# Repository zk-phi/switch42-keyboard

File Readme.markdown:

Switch42 Keyboard の紹介＆組み立てガイド

(これは基板バージョン rev3 ベースの紹介です)

# 概要

Switch42 は zk-phi が初めて設計した自作キーボードキットです。

以下の特徴があります：

- 直行配列・分割キーボード

- Corne Keyboard などとちょうど同じ 42 キー
  - (ホームポジションからひとマスで到達できる行・列が過不足なくついています)

- 指の腹で押せるよう、少し張り出して配置した親指キー

- フルカラー LED / LED テープに対応

- ProMicro を下部に格納し、スッキリした外観

- MX 互換スイッチ専用

- (非リバーシブル基板で表裏を間違いづらい)

LED 以外には表面実装品を使わないので、組み立て難易度は初〜中級者向けだと思います。二箇所だけ一般的な自作キーボードキットには出てこない作業が登場します：

- 基板の不要部分をカットする作業
- Pro Micro と干渉する部品の足をカット・絶縁

# 設計の経緯＆工夫など
## なぜ作ったの？

Ergo42 で自作キーボードデビューしてから、よりキー数の少ない Corne に挑戦し、使っているうちにこんな実感が湧いてきました：

- このキー数でも十分仕事になるけど、これより少ないくなると自分には辛いな
  - = これがコンパクトさと実用性の落としどころだな

6 x 3 + 3 というキー配列に大満足していた一方で、だんだんと Ergo42 の格子配列も恋しくなってきたりもして、ヨシそれなら「格子配列の 42 キー」を作ってみよう、と設計に挑戦しました。

オリジナルな工夫もなにか入れたいなということで、以前から気になっていた「親指キー押しづらい問題」に対する自分なりのアイデア（張り出させて配置する）も盛り込んでみました。

また、それまで LED のハンダづけにビビってキーボードを光らせてこなかったのですが、自分で設計すればきっと試作基板がたくさん余るので失敗も怖くないぞ！ということで、初のキーボード設計から LED 対応に挑戦しました。

同じ「格子配列＋親指キー」ということで、 コンセプトの近い MiniAxe を組むことも考えたのですが、以下のポイントが決め手になって、自分で設計することにしました：

- ６列キーボードが絶対必要だったこと

自分は Emacs のヘビーユーザーで、 Alt-Ctrl-, Alt-Shift- などの複雑な組み合わせにもいちいちショートカットを設定しているので、 Ctrl, Shift を小指で押せる仕様がマストでした。

- Pro Micro を採用したかったこと

MiniAxe は定番のマイコンボード "Pro Micro" を採用しない、より進んだ設計になっています。これによって、とても薄く、「モゲ」問題とも無縁なキーボードを実現しています。一方、半田付け難易度は Pro Micro を使用したキーボードよりも上がっていて、組み立てられるか不安だったのと、自分以上に初心者な友人に提供したかったこともあったので、オーソドックスな Pro Micro (コンスルー) を採用したいモチベーションがありました。

## 設計上の工夫

リバーシブル基板をやめて、代わりに基板の不要部分を切り取れるようにしました。もともとは ProMicro を下部に格納しつつコンスルーに対応するために考えた仕様でしたが、結果的に部品の向きを間違えるミスも減らせてよかったんじゃないかなと思っています。

# 組み立てガイド
## オプション

以下の箇所は組み立て方に選択肢があるので、好みでカスタマイズしてください。

- Pro Micro などを覆う底板を省略することで、 3mm ほど薄くすることができます

- LED をつけることがきます (難しいです。つけなくても使えます)

## 必要な部品 (両手分)

- Switch42 専用部品
  - 基板 2 枚
  - トッププレート 2 枚
  - ボトムプレート (穴あき) 2 枚 [左右別]
  - 底板 (穴なし) 2 枚

- 汎用電子部品
  - ダイオード [1N4148 / 1N4148w] 42 個
  - TRRS ジャック [MJ-4PP-9] 2 個
  - タクトスイッチ [TVBP06] 2 個
  - コンスルー (スプリングピンヘッダ) 付き Pro Micro 2 セット
  - MX 互換キースイッチ 42 個
  - MX スイッチ用キーキャップ 42 個
  - 光らせたい場合はどちらか選択:
    - WS2812B の LED テープ (幅 1cm) 2 本 [簡単]
    - SK6812mini 42 個 [難しい]
  - 絶縁テープ (カプトンテープなど)

- ケースの組み立て材
  - M2 スペーサ 7mm 10 本
  - クッションゴム 10 個
  - 底板をつけるどうかによって選択:
    - M2 ネジ 5mm 20 本 [底板なし]
    - M2 ネジ 8mm 20 本 [底板あり]

- ケーブル類
  - Micro USB ケーブル
  - TRRS ケーブル

- あると便利なもの
  - マスキングテープ

※ダイオードは表面実装品でもリード部品でも ok です。初めての場合はリード部品を選択しましょう。

※コンスルーは必須ではないですが、リカバリや修理が簡単になるので強く推奨します

## 主な爆死ポイント

組み立てる時はチェックしましょう。

- 定番
  - ハンダ不良
  - ProMicro / ダイオードの向き間違い
  - トッププレートをはめずにキースイッチをつけてしまう
  - TRRS ジャック、リセットスイッチをつける前にキースイッチをつけてしまう
  - トッププレートを割る
  - (ProMicro の MicroUSB 端子モゲ)

- Switch42 特有
  - 基板の不要部分をカットするときに、必要な部分も破壊してしまう
  - 絶縁テープを貼り忘れる (コンスルーならリカバリー可)

## 組み立て手順

組み立ての手順を順に紹介してゆきます。

ハマりどころはなるべくフォローしてゆくつもりで書いていますが、半田付け自体の基本的な知識、たとえば道具の持ち方・使い方、ハンダ不良の見分け方などはより詳しい資料があるはずなので、そちらで復習しておくと確実です。

### Pro Micro の準備
#### Pro Micro にファームウェアを書き込む

Pro Micro にファームウェアを書き込みます。

私のリポジトリ (https://github.com/zk-phi/qmk_firmware) からコードをダウンロード後、QMK Firmware の公式ページを参考に環境を構築します。

キーボードを光らせるためにテープ LED を使用する場合、 qmk_firmware/keyboards/switch42/keymaps/default/config.h の「USE_BAKCLIGHT」 の行をコメントアウトします。

環境ができたら、 Pro Micro を USB で接続した上で

```terminal
make switch42/rev1:default:avrdude
```

を実行し、 Pro Micro の `GND` ピンと `RST` ピンをピンセットなどでショートすることで書き込むことができます。

初期不良の確認も兼ねて、２台とも書き込んでしまいましょう。後から書き換えも可能です。

#### Pro Micro にコンスルーを立てる

LED の動作確認ですぐに使うので、 Pro Micro にあらかじめコンスルーを取り付けておきます。

向きが少しややこしいので注意して下さい：

コンスルーのプラスチック部分に空いた穴に注目します。 *穴の空いている方が「Pro Micro」側になるように、また二つのコンスルーで穴が同じ方を向くように、* コンスルーを Pro Micro に差し込みます。 *Pro Micro の「部品が乗っている面と同じ面に」* コンスルーを立てます。

斜めになってしまわないように注意しながら半田付けします。

詳細は (Helix のビルドガイド)[https://github.com/MakotoKurauchi/helix/blob/master/Doc/buildguide_jp.md#pro-micro] に詳しいです。

### PCB の準備

基板は右手用・左手用で同じものを使います。スイッチの乗りそうな四角がたくさん並んでいる方が表です。

２枚の基板を同じ向きで（たとえば、表を上に）置いて、 *一方は左の、他方は右の、* 親指クラスタを落とします。同じ側を落として右手・右手や左手・左手のキーボードになってしまわないように注意してください。

力技で折ろうとすると、写真のように基板を損傷します。

*ニッパやカッターなどであらかじめ傷をつけて、* なるべく少ない力で折り取ります。切りしろ部分以外に傷をつけないように注意してください。最悪、そこを通っている配線を断線してしまうと、動作に問題が起こる場合があります (特に LED)。バリはある程度残したままでもケースに収められるようになっています。うっかり傷つけるくらいならそのままにしましょう。

### SK6812mini をつける (光らせる場合)

SK6812mini を半田付けしてゆきます。コの字の印のあるパッドが SK6812mini の Vcc になります。

基板の個体差で LED が穴に落ちてしまう場合、マスキングテープで軽く固定するとつけやすくなります。

熱で壊れやすいので、高くとも 270 度程度に抑えて半田付けします。

LED は図のように直列に並んでいるので、一つ目から順に半田付けし、都度次のように動作確認すると安全です：

1. 基板にコンスルー付き Pro Micro を差し込む
2. USB ケーブルを刺して PC やモバイルバッテリーから電源を供給
3. 光れば ok

Pro Micro は写真のように、基板にプリントされた枠線に合わせて差し込みます。

ハンダは付いているのに光らない LED がある場合、おそらく熱で壊れているので、ハンダを丁寧に除去し、基板のパッドを剥がさないように慎重に LED だけを外します（外れない場合、無理に力を加えずに、ハンダを除去し直してください）。

### ダイオードをつける

キー数分のダイオードをつけてゆきます。表面実装品・リード部品から好みの方を選んで取り付けることができます。

ダイオードには向きがあるので注意してください。リード部品の場合、基板の表側から、印刷されたアイコンと同じ向きで挿入します。表面実装品の場合、基板裏面のパッドに、 *カソードがコの字の印のところに来るように* 乗せます。

LED をつけた場合、ここからはコテの温度を元に戻して構いませんが、 *高温のコテで LED に触ってしまって、せっかく取り付けた LED を破壊することがないように* 注意してください。

余談ですが、プレート２枚と基板１枚を重ねると、ダイオードの足を曲げるのにちょうどいい厚さになります。

### リセットスイッチ、TRRS ジャック をつける

リセットスイッチ、 TRRS ジャックをこの順にとりつけます。順番を間違えても致命傷にはなりませんが、先に背の高い部品をつけてしまうと、後から背の低い部品をつけるのは若干厄介です。

基板の裏面に取り付け位置の目印があるので、ここに取り付けます。

### Pro Micro を差し込み、動作確認をする

以降の手順を終えるとリカバリの難易度が一気に上がるので、ここで 一度 Pro Micro を装着し、動作確認をします。

- [LED] LED が光るか
- [ダイオード] スイッチが入る予定のピンをピンセットなどで直接ショートした時、キー入力が行われるか
- [TRRS] TRRS ケーブルで左右を繋いだ時、 USB が直接刺さっていない側のキーボードからもキー入力ができるか
- [リセットスイッチ] ファームウェア書き込み時のリセット操作を、タクトスイッチで代用できるか

### トッププレート・キースイッチをつける

*トッププレートにキースイッチをはめ、* 基板とドッキングします。

プレートの保護シートはスイッチをはめてから剥がすと、指紋をつけにくいです。

トッププレートを挟まずに直接スイッチを取り付けてしまうと、後からトッププートを組み込むことができなくなります。

基板からスイッチが浮いてしまわないよう、しっかり押し付けます。プレートは基板に押しつける必要はありません。基板とプレートの間に 2mm ほど隙間がある状態が正しいです。

無事ドッキングできたら、キースイッチを半田付けします。

このとき、 *Pro Micro が上に重なるところのスイッチだけは、あらかじめ足をカットしておき、基板とツライチで* （飛び出さないように）半田付けをします。その後、 *絶縁テープを貼って Pro Micro に触れないようにします* 。耐熱のカプトンテープなどがあれば理想的です (私はビニテを貼っています。。)。デザイン上の都合で Pro Micro をここに装着するしかなかったため、やむを得ずこのような手順になっています。

### LED テープをつける

LED テープを使ってキーボードを光らせる場合、基板裏面のパッドに合わせて LED テープをベタッと貼り付け、半田付けします。 DOUT ではなく DIN を接続するように注意してください。

LED テープは長すぎる場合、適宜な箇所でカットすることができます。

### Pro Micro を装着、ケースを組み立てる

スイッチを無事取り付けることができたらハンダ作業はこれでおしまいです。Pro Micro をもう一度取り付け、ケースを組み立てます。

トッププレートにネジを使ってスペーサーを立てて、ボトムプレートと合体します。ボトムプレートは左右で形状が違うため注意してください。底板を使う場合は、ボトムプレートの下にさらに底板を重ね、長め (8mm) のネジで貫通するようにとめます。使わない場合は短め (5mm) のネジでとめます。

ケースが組めたら、クッションゴムを貼り付け、キーキャップを装着して完成です。

### おまけ: マステ Mod について

Underglow を使用する場合、写真のように真下にマスキングテープなどを貼り付けると、光が拡散しボトムプレート全体を光らせることができます。

## デフォルトキーマップの紹介

デフォルトのキーマップは次のようになっています。

単にキーを押すと、黒字のキーが入力されます。「英数 Alt」のように二つの機能が書かれているキーは、単独で押すと「英数」として、長押しすると「Alt」として機能します。「英数」「かな」は Mac 用のキー、「全角半角」は Windows 用のキーです。

橙のキー（「かな」）を押しながら他のキーを押すと、橙の字で書かれたキーが入力されます。数字や各種記号の入力にはこれを使います。

青のキー（「Esc」）を押しながら他のキーを押すと、青の字で書かれたキーが入力されます。主にファンクションキーなど、特殊なキーを入力するために使います。

緑のキー（「D」）を押しながら「HJKL」キーを押すと、マウスを操作できます。さらに「F」キーも同時に押すと、マウスカーソルの代わりにスクロールホイールを操作できます。

### ガラケーモードについて

橙のキー（「かな」）を押しながら「Tab」を押すと「ガラケーモード」に突入します。 LED が実装されている場合、ガラケーモードになっているかどうかは LED の色で識別できます。

このモードでは、同じキーの連打回数によって異なるアルファベットを入力でき、 Switch42 を片手キーボードとして利用できます。たとえば、「abc」キーを 2 回連打すると「b」が入力されます。

ガラケーモードでも同様に、橙のキーを押しながら他のキーを押すと、マウス操作、ホイール操作などを行うことができます。

「テンキー」キーを押すとテンキーモードとなり、緑の文字で示された数字を入力できるようになります。もう一度「テンキー」キーを押すことで通常のガラケーモードに戻ります。

左手の右下キー「終了」を押すとガラケーモードを終了します。

### キーマップの書き換え

キーマップの定義は qmk_firmware/keyboards/switch42/keymaps/default/keymap.c にあります。このファイルを編集し、あらためてファームウェアの書き込み作業を行うことで、キーマップを変更できます。

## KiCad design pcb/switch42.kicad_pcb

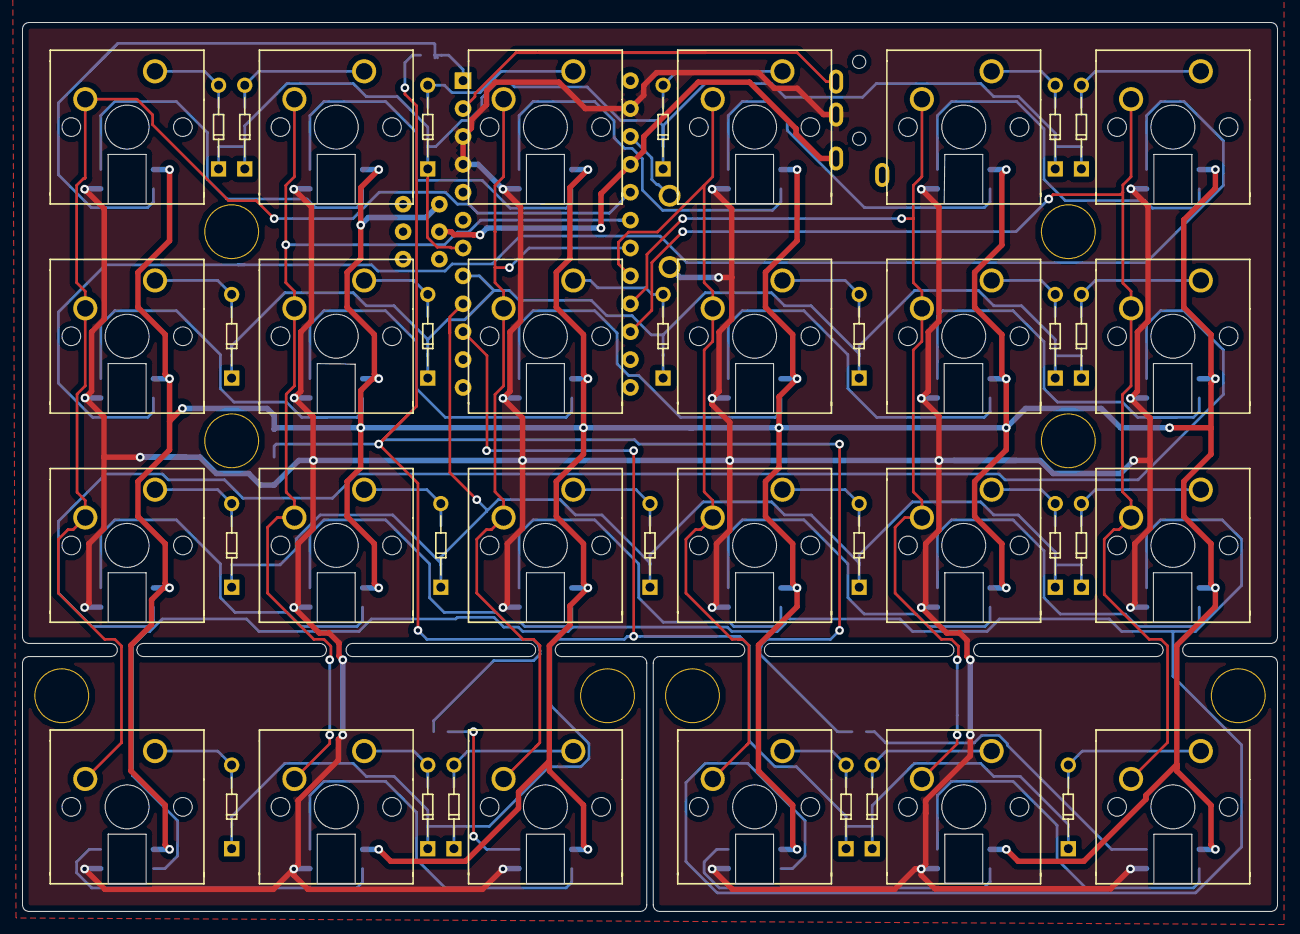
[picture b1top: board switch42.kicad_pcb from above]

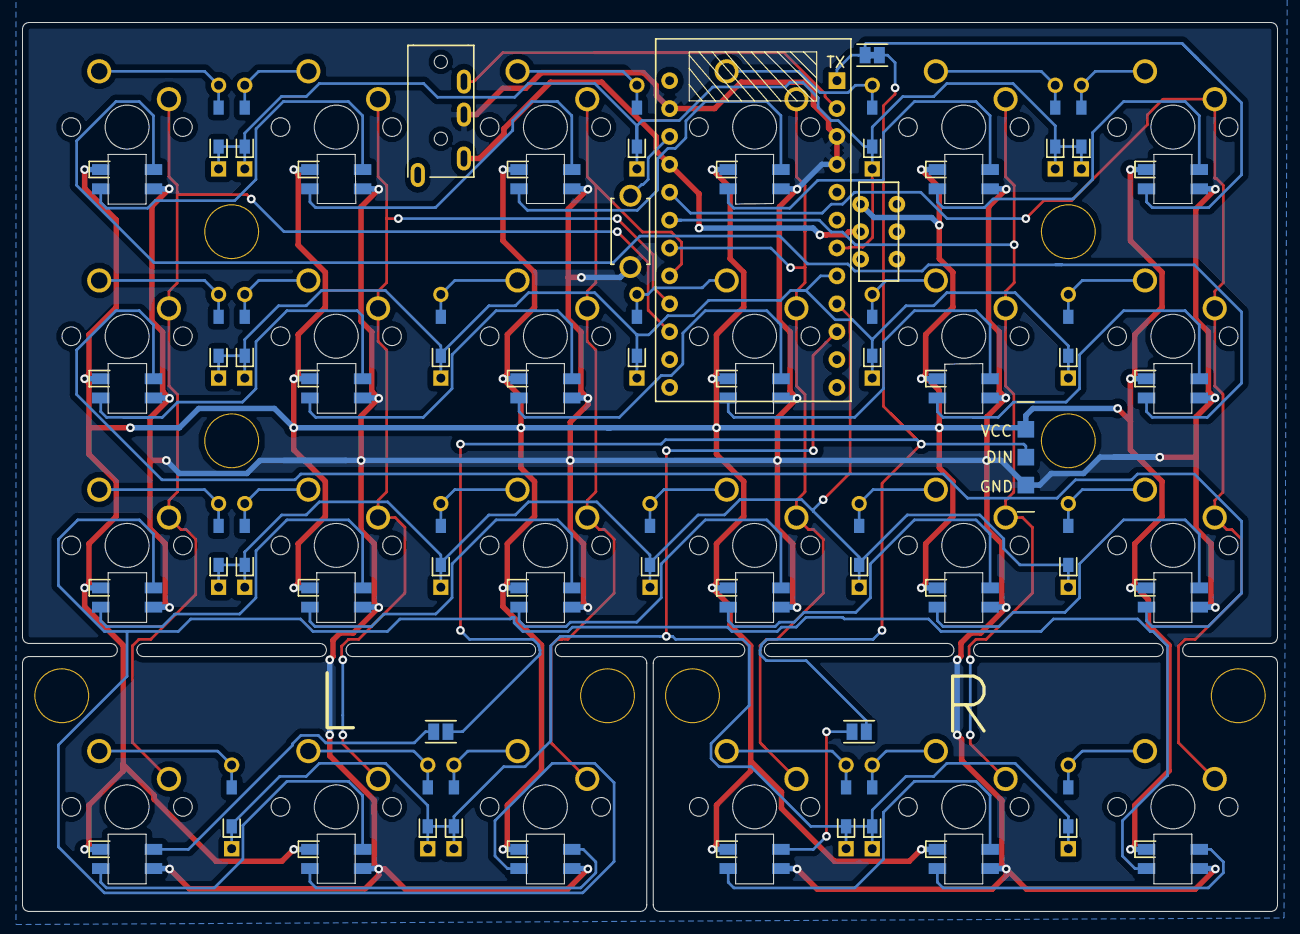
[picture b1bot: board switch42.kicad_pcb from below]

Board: 2 copper layers, 114.3 x 81.0 mm, 88 parts (32 on the bottom side), 65 nets.

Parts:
D1, D2, D3, D4, D5, D6, D7, D8, D9, D10, D11, D12, D13, D14, D15, D16, D17, D18, D19, D20, D21, D22, D23, D24: D; D_TH_SMD-irreversible
J1: MJ-4PP-9; MJ-4PP-9-irreversible
J2: Conn_01x03; StripLED-1mm-irreversible
JP1: Jumper; Jumper-Closed
JP2, JP3: Jumper_NO_Small; Jumper-Open
L1, L2, L3, L4, L5, L6, L7, L8, L9, L10, L11, L12, L13, L14, L15, L16, L17, L18, L19, L20, L21, L22, L23, L24: SK6812MINI; SK6812MINI-irreversible
Ref**: Val**; HOLE
Ref**#2, Ref**#3, Ref**#4, Ref**#5, Ref**#6, Ref**#7, Ref**#8: Val**; HOLE
SW1: SW_PUSH; ResetSW-irreversible
SW2, SW3, SW4, SW5, SW6, SW7, SW8, SW9, SW10, SW11, SW12, SW13, SW14, SW15, SW16, SW17, SW18, SW19, SW20, SW21, SW22, SW23, SW24, SW25: SW_PUSH; MX_1.00u-irreversible
SW26: SW_DPDT_x2; IS-2235-irreversible
U1: ProMicro; ProMicro_Reversed_Conthrough-irreversible

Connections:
GND: J1.C, J2.3, L1.2, L2.2, L3.2, L4.2, L5.2, L6.2, L7.2, L8.2, L9.2, L10.2, L11.2, L12.2, L13.2, L14.2, L15.2, L16.2, L17.2, L18.2, L19.2, L20.2, L21.2, L22.2, L23.2, L24.2, SW1.2, U1.3, U1.4, U1.23
unnamed: D1.2, SW2.2
unnamed: D2.2, SW3.2
unnamed: D3.2, SW4.2
unnamed: D4.2, SW5.2
unnamed: D5.2, SW6.2
unnamed: D6.2, SW7.2
unnamed: D7.2, SW8.2
unnamed: D8.2, SW9.2
unnamed: D9.2, SW10.2
unnamed: D10.2, SW11.2
unnamed: D11.2, SW12.2
unnamed: D12.2, SW13.2
unnamed: D13.2, SW14.2
unnamed: D14.2, SW15.2
unnamed: D15.2, SW16.2
unnamed: D16.2, SW17.2
unnamed: D17.2, SW18.2
unnamed: D18.2, SW19.2
unnamed: D19.2, SW20.2
unnamed: D20.2, SW21.2
unnamed: D21.2, SW22.2
unnamed: D22.2, SW23.2
unnamed: D23.2, SW24.2
unnamed: D24.2, SW25.2
unnamed: JP2.1, L12.1
unnamed: JP3.1, L24.1
unnamed: L1.1, L5.3
unnamed: L2.1, L6.3
unnamed: L2.3, L21.1
unnamed: L3.1, L7.3
unnamed: L4.1, L8.3
unnamed: L5.1, L9.3
unnamed: L10.1, L14.3
unnamed: L6.1, L10.3
unnamed: L11.1, L15.3
unnamed: L7.1, L11.3
unnamed: L8.1, L12.3
unnamed: L13.1, L17.3
unnamed: L9.1, L13.3
unnamed: L14.1, L18.3
unnamed: L15.1, L19.3
unnamed: L16.1, L20.3
unnamed: L4.3, L16.3, L23.1
unnamed: L17.1, L21.3
unnamed: L18.1, L22.3
unnamed: L19.1, L23.3
unnamed: L20.1, L24.3
unnamed: L3.3, L22.1
VCC: J1.D, SW26.2, U1.21
col0: SW2.1, SW3.1, SW4.1, SW5.1, U1.20
col1: SW6.1, SW7.1, SW8.1, SW9.1, U1.19
col2: SW10.1, SW11.1, SW12.1, SW13.1, U1.18
col3: SW14.1, SW15.1, SW16.1, SW17.1, U1.17
col4: SW18.1, SW19.1, SW20.1, SW21.1, U1.16
col5: SW22.1, SW23.1, SW24.1, SW25.1, U1.15
data: J1.B, U1.2
led: JP1.1, L1.3, U1.1
ledpower: J2.1, L1.4, L2.4, L3.4, L4.4, L5.4, L6.4, L7.4, L8.4, L9.4, L10.4, L11.4, L12.4, L13.4, L14.4, L15.4, L16.4, L17.4, L18.4, L19.4, L20.4, L21.4, L22.4, L23.4, L24.4, SW26.3
reset: SW1.1, U1.22
row0: D1.1, D5.1, D9.1, D13.1, D17.1, D21.1, U1.7
row1: D2.1, D6.1, D10.1, D14.1, D18.1, D22.1, U1.8
row2: D3.1, D7.1, D11.1, D15.1, D19.1, D23.1, U1.9
row3: D4.1, D8.1, D12.1, D16.1, D20.1, D24.1, U1.10
underglow: J2.2, JP1.2, JP2.2, JP3.2

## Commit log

2019-01-02 Rename dirname
2019-01-02 Add script to rename gerber files
2019-01-04 Add case model
2019-01-08 Refactoring: Remove unused fn
2019-01-08 Add keycaps to the case preview model
2019-01-08 Add option thumb_margin to the case model
2019-01-09 Add margin to case model
2019-01-09 Add margin and mask, silk to the pcb
2019-01-10 Add comment to easily preview with KiCad-exported stl
2019-01-10 Refactoring: Skrew hole related things in the case model
2019-01-11 Change skrew positions and thumb margin
2019-01-12 Change footprint of TRRS and ProMicro
2019-01-12 Add silks to the switches, and adjust promicro/trrs position
2019-01-12 Thinner silks for promicro and thinner margin between two thumb clusters
2019-01-12 Update skrew positions of the case model
2019-01-12 Fix measurement
2019-01-12 .gitignore backup files
2019-01-12 Fix ProMicro and TRRS height
2019-01-12 Switch to KiCad STEP UP to generate PCB preview
2019-01-12 Use 3mm acrylic plate instead of 2mm
2019-01-12 Add 300x300 cut model
2019-01-12 Tweak color of preview model
2019-01-13 Make PCB preview white
2019-01-13 .gitignore .bak files
2019-01-14 Remove an unused screw hole
2019-01-14 Change silks
2019-01-17 Slightly modify footprint silks
2019-01-17 Refactoring: Reduce redundant vias
2019-01-17 Add pads for LED strip and uniform the weight of silk text
2019-01-17 Remove gomuashi holes from the very bottom plate
2019-01-18 Change silk texts for the LED strip
2019-01-23 Make diode line around thumb clusters safer
2019-01-24 Make preview 7mm-spacer spaced as actual
2019-01-25 Change version name
2019-01-25 Add experimental case model with middle plates
2019-01-25 Use phi-kbd-library symbols
2019-01-27 Use components from my own library
2019-01-27 Update LED strip footprint and adjust position, silk
2019-01-31 Fix GND fill
2019-01-31 Add cut model for middle plates
2019-01-31 Add spacers to the preview model
2019-02-21 Fix silk position
2019-02-22 Add jumpers to use underglow alongside backlights / update footprints
2019-02-25 Clarify comment
2019-02-25 Add slide sw to toggle LEDs
2019-02-25 Control VCC with the slide sw, instead of LED signals
2019-02-26 Update StripLED footprint
2019-04-13 Add readme.markdown
2019-04-13 Fix image paths
2019-04-13 Add information about USE_BACKLIGHT
2019-04-13 Add how to remap keys
2019-05-13 Add LICENSE
